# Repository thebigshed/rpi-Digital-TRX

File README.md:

# rpi-Digital-TRX

A stand-alone digital voice network radio on a Raspberry Pi 4 or Pi Zero 2 W. It is the hardware version of
[Digital Transceiver](https://github.com/thebigshed/digital-transceiver): it listens and
transmits on DMR, D-Star, YSF, P25, NXDN and M17, and receives DAPNET pages, over Wi-Fi.
There's no desktop. It boots straight into the radio, and you drive it from a front panel: mode
buttons with RGB LEDs, a channel knob, a volume knob and a PTT button, with a 20×4 LCD.

## Hardware

| Part | Used for | Connection |
|---|---|---|
| Raspberry Pi 4, or Pi Zero 2 W | Runs everything | — |
| NW Digital Radio DV3000 (ASSY1101, AMBE-3000R) | AMBE / AMBE+2 encode and decode in hardware: DMR, D-Star, YSF (DN), NXDN | First 26 header pins: serial port `/dev/ttyAMA0` at 230400 baud, reset on GPIO 4 |
| 20×4 LCD (HD44780) with a PCF8574 I2C backpack | Display | I2C at 0x27 or 0x3F, on the 5 V side of an I2C level shifter |
| Front panel ([wiring](docs/wiring.md)) | Six mode buttons, Menu, PTT, two KY-040 rotary encoders (channel and volume) | GPIO, through a 40-pin splitter |
| Two MCP23017 I/O expander modules | The seven common-cathode RGB LEDs (six modes and status) | I2C at 0x21 and 0x22, powered from 5 V on the 5 V side of the level shifter |
| USB headset | Speaker and microphone; its call button toggles PTT | USB |
| Adafruit RGB LCD Pi Plate (optional) | The old display and five buttons, used if the 20×4 isn't fitted | I2C at 0x20 |

The AMBE board sits on the first 26 header pins, and the panel is wired to the other side of a
"1 to 2" header splitter. They use different pins: the AMBE board uses the serial port
(GPIO 14/15) and GPIO 4, and the panel uses I2C (GPIO 2/3) and other GPIO pins. See
[docs/wiring.md](docs/wiring.md).

### Codecs

| Mode | Codec | Where it runs |
|---|---|---|
| DMR, NXDN, YSF DN | AMBE+2 | AMBE board |
| D-Star | AMBE | AMBE board |
| P25, YSF VW | IMBE | Software (OP25 / mbelib), easily fast enough on a Pi 4 |
| M17 | Codec2 | Software |

## Design

- **OS**: a minimal Linux image built with [Buildroot](https://buildroot.org) (2026.02 LTS).
  It has no desktop. It holds only what the radio needs: Qt 6 Core and Network (no Qt GUI,
  fonts or display platform), PulseAudio (system mode), wpa_supplicant, chrony, Dropbear SSH and
  i2c-tools.
- **App** (`app/`): the radio. It started as the Digital Transceiver desktop app and is now
  cut down to what the Pi needs: there are no windows or dialogs, and it is a plain Qt Core
  program. It is in three layers:
  - `Radio` (`Radio.cpp`, `RadioNet.cpp`): networks, decoding, calls, transmit, logs and
    recordings. It has no user interface.
  - `FrontPanel`: what the display shows and what each control does. It knows nothing about
    the hardware: displays implement `Display`, and input devices call `press()`,
    `release()`, `turn()` and `togglePtt()`.
  - Hardware: `GpioPanel` (the panel's buttons and encoders, as kernel GPIO events),
    `LedPanel` (the LEDs), `Lcd2004` (the 20×4 display), `LcdPlate` (the old 16×2 plate), `HeadsetButtons` (the
    headset's call button) and `SimPanel` (a stand-in for testing on a PC). Each part is
    optional; the radio logs what it can't find and carries on.

  Settings, call logs and recordings are the same as the desktop app's, so its
  `settings.json` can be copied over.
- **Display** (20×4):

  ```
  DSTR REF001 E  12:41     TX mode, where it transmits, time
  M6OZE            DSTR    the call on air: callsign and mode
  Ozzy                     name
  >CQCQCQ          0:07    target and call time
  ```

  When no call is on air, lines 2 and 3 show the last call heard, and the bottom line shows the
  IP address and volume, or a problem (a failed login, or the Pi-Star online). While browsing destinations it
  shows the one selected and the next. If the 20×4 isn't fitted, the Adafruit plate's 16×2
  shows a two-line version.
- **Controls** (full details in [docs/wiring.md](docs/wiring.md#what-the-controls-do)):

  | Control | Action |
  |---|---|
  | Mode button | Tap: listen to the mode or not. Hold: make it the TX mode |
  | Channel knob | Turn: step through the TX mode's destinations (reflectors, talkgroups, and for DMR the talkgroups listed in `settings.json`). Push: go there. Push and turn: D-Star / M17 module letter |
  | Volume knob | Turn: volume. Push: mute |
  | PTT | Hold to talk |
  | Menu | Tap: back. Hold 3 s: shut down; unplug when the display says "Safe to unplug" |
  | Headset call ("Teams") button | PTT on / off: press to start transmitting, press again to stop (the button only clicks, so it can't be held) |
  | LCD plate | Select: PTT, or go to the destination shown. Up / Down: TX mode. Left / Right: browse |

- **LEDs**: each mode's LED is green when listening, red when it's the TX mode (yellow for
  both) and blue while a call is on air in it. The status LED is red while transmitting, green
  while receiving and blue for a network problem or an unread page.

- **AMBE board**: the app opens the DV3000 with `--ambe /dev/ttyAMA0`. It resets the board on
  GPIO 4 (header pin 7) and talks to it at 230400 baud using DVSI's packet protocol
  (`app/src/AmbeChip.cpp`).
  - D-Star frames go to the chip as they are.
  - DMR, YSF DN and NXDN go to the chip as the 49 AMBE+2 voice bits, after mbelib's error
    correction (rate 34). The chip's bit order differs from mbelib's; the mapping was measured
    on the chip and is built in.
  - The chip has one decoder, so it follows one call at a time; any other call is decoded in
    software.
  - P25 (IMBE) and M17 (Codec2) are always decoded in software.
  - Check a chip with
    `digital-transceiver --ambe /dev/ttyAMA0 --ambe-test recording.wav`. It runs a recording
    through every chip and software combination and compares the result.

## Building

| Board | Command | Image |
|---|---|---|
| Raspberry Pi 4 | `./build.sh` | `output/images/sdcard.img` |
| Raspberry Pi Zero 2 W | `BOARD=zero2w ./build.sh` | `output-zero2w/images/sdcard.img` |

The first build for a board fetches Buildroot 2026.02.3 (once) and builds everything, which
takes a while. Each board has its own output folder, and the downloaded sources are shared. The
app is built from `app/` in this project. To rebuild only the app after changing it, run
`./build.sh digital-transceiver-rebuild all`, with `BOARD=zero2w` in front for the Zero.

`build.sh` reconfigures Buildroot when `external/configs/dtrx.fragment` or the board's fragment
changes. Buildroot leaves removed packages in the image until a clean build, so after removing
any, run `./build.sh clean all`.

### Raspberry Pi Zero 2 W

The Zero 2 W image runs the same software with the same hardware: the DV3000 fits the first 26
header pins, and the front panel wiring is unchanged. The differences are:

- **USB:** the headset goes in the **USB** port (the inner micro-USB, not PWR IN) through a
  micro-USB OTG adapter. Anything else needs a small hub.
- **No Ethernet:** Wi-Fi is the only network, so `wpa_supplicant.conf` must be on the boot
  partition before the first boot. Wi-Fi is 2.4 GHz only.
- **No analog audio:** the USB headset is the only audio device.
- **Header:** the plain Zero 2 W has no header fitted. Use a "WH" board, or solder one on.
- **Power:** a 5 V 2.5 A supply is plenty.

### Trying the app on a PC

The app also builds on a Linux PC with Qt 6 (Core and Network) and, for M17, Codec2:

```sh
cmake -S app -B app/build && cmake --build app/build -j
app/build/digital-transceiver --sim
```

With `--sim` (or `--sim-16x2` for the plate's layout), the display and LEDs are printed to the terminal and the controls are typed, one
per line (`+` = press, `-` = release): `1+`…`6-` the mode buttons, `t+`/`t-` and `v+`/`v-` turn
the channel and volume knobs, `k+`/`k-` push the channel knob, `m` pushes the volume knob,
`p+`/`p-` is PTT, `n+`/`n-` Menu and `h` the headset button. `s`, `u`, `d`, `l` and `r` are the
LCD plate's buttons. It uses the PC's settings in
`~/.config/digital-transceiver/digital-transceiver/`, so it logs in to the networks with
them; don't run it while the radio or the desktop app is online with the same IDs.

## Setting up the SD card

1. Write the board's image to the card (`output/images/sdcard.img` for the Pi 4,
   `output-zero2w/images/sdcard.img` for the Zero 2 W), for example with
   `sudo dd if=output/images/sdcard.img of=/dev/sdX bs=4M conv=fsync`. Write to the whole card
   (`/dev/sdX`), not a partition (`/dev/sdX1`).
2. On the card's boot partition (FAT, readable on any PC), add:

   | File | What it's for |
   |---|---|
   | `wpa_supplicant.conf` | Your Wi-Fi network; copy `boot-examples/wpa_supplicant.conf` and fill it in |
   | `settings.json` | Your Digital Transceiver settings; copy the desktop app's `~/.config/digital-transceiver/digital-transceiver/settings.json` |
   | `authorized_keys` | Optional: SSH public keys, for `ssh root@dtrx` |

   `settings.json` is copied in on the first boot and then renamed `settings.json.applied`, so
   changes made on the radio are kept.
3. Plug in the USB headset and boot. To turn the radio off, hold Menu for 3 seconds and unplug
   it when the display says "Safe to unplug". The app's log is `/var/log/dtrx.log`, and its event log
   is in `/root/.local/share/digital-transceiver/digital-transceiver/events.log`.

Don't run the radio and the desktop app (or a Pi-Star) at the same time with the same
settings: they would log in to the networks with the same IDs. Give the Pi its own DMR hotspot
ID (for example your DMR ID plus `03`) in its `settings.json`.

## Layout

```
build.sh            Configure and build the SD card image
app/                The radio app (CMake, Qt 6 Core and Network)
  src/              Radio, FrontPanel, the hardware drivers, decoders and network clients
  third_party/      mbelib (AMBE / IMBE decoding) and the OP25 vocoder (encoding)
external/           Buildroot external tree (BR2_EXTERNAL "DTRX")
  configs/          dtrx.fragment (all boards), rpi4.fragment and zero2w.fragment: added to
                    Buildroot's raspberrypi4_64 / raspberrypizero2w_64 defconfig
  package/          codec2, and digital-transceiver (built from app/)
  board/common/     post-build.sh and the rootfs overlay, for all boards
                    (init scripts: boot-partition config, Wi-Fi, the app)
  board/rpi4/       Pi 4 firmware config.txt and cmdline.txt
  board/zero2w/     Zero 2 W firmware config.txt and cmdline.txt
boot-examples/      Example files for the boot partition
buildroot/          Buildroot (fetched by build.sh, not committed)
output/             Pi 4 build output (not committed)
output-zero2w/      Zero 2 W build output (not committed)
```

## Next steps

1. **Menu**: a menu for RX modes, DMR talkgroup, volume and IP address (a long Menu press is
   now shutdown, so it will need another way in, such as pushing both knobs).

## Licence

GPL-3.0-or-later, the same as Digital Transceiver, whose code it reuses. mbelib (`app/third_party/mbelib`)
and OP25 (`app/third_party/op25_vocoder`) keep their own licences.

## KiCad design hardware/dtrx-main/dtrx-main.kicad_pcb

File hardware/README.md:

# Digital TRX hardware (KiCad 9)

Two boards joined by a 20-way IDC ribbon cable (pin 1 to pin 1):

| Project | What's on it |
|---|---|
| `dtrx-main/` | Raspberry Pi Zero 2 W (face down on a 2x20 socket, ports at the left edge), the DV3000 AMBE-3000 board on a 2x13 header, 5 V input with a PTC fuse, and the ribbon header |
| `dtrx-panel/` | The front panel: 20x4 LCD in the middle, three mode buttons with RGB LEDs down each side, volume encoder and Menu bottom left, PTT and channel encoder bottom right, the status LED under the display. J2 for the LCD's I2C backpack. On the back: both MCP23017 LED drivers, the I2C level shifter and the pull-ups |

Open `dtrx-main/dtrx-main.kicad_pro` or `dtrx-panel/dtrx-panel.kicad_pro` in KiCad. Each has a
schematic, a routed 2-layer PCB with a ground pour on both sides, and a PDF of the schematic.

Both boards were autorouted with Freerouting by `route.py`, ground included, so no pin depends
on the pour. DRC is clean on both boards: every connection made, the PCB matching its schematic,
no warnings. Where tracks box a ground pin in so the pour's thermal spokes can't reach it,
`route.py` connects that one pin solidly to the pour instead (a handful of header pins).

The design matches the app as it is. Buttons and encoders go to the same Pi GPIO pins, the LED
drivers sit at 0x21 and 0x22, and the LCD keeps its own I2C backpack (0x27 or 0x3F). So no
software changes are needed apart from building the image for the Pi Zero 2 W.

## Regenerating

`gen_boards.py` writes both projects from scratch: `python3 hardware/gen_boards.py` (it needs KiCad's
`pcbnew` Python module). Re-running it **overwrites** any routing or hand changes, so make design
changes in the script first, then route again with `python3 hardware/route.py` (needs Java and the
[Freerouting](https://github.com/freerouting/freerouting/releases) jar; see the top of the script). Part values, pin assignments, positions and the LCD
dimensions are all near the top of the script.

## Ribbon (J3 on the main board, J1 on the panel)

| Pin | Signal | Pin | Signal |
|---|---|---|---|
| 1 | +5 V | 2 | GND |
| 3 | +3.3 V | 4 | SDA (3.3 V) |
| 5 | SCL (3.3 V) | 6 | GND |
| 7 | PTT (GPIO 23) | 8 | Menu (GPIO 26) |
| 9 | Channel A (GPIO 24) | 10 | Channel B (GPIO 27) |
| 11 | Channel push / Link (GPIO 22) | 12 | Volume A (GPIO 20) |
| 13 | Volume B (GPIO 21) | 14 | Volume push / Mute (GPIO 18) |
| 15 | DMR (GPIO 5) | 16 | D-Star (GPIO 6) |
| 17 | YSF (GPIO 12) | 18 | P25 (GPIO 13) |
| 19 | NXDN (GPIO 19) | 20 | M17 (GPIO 16) |

The I2C bus crosses the ribbon at 3.3 V, and a two-FET level shifter on the panel lifts it to 5 V
for the MCP23017s and the LCD backpack. So the LEDs and the LCD run from 5 V, as on the hand-wired
panel. The MCP23017 address pins are fixed by copper (no jumpers to bridge): U1 is 0x21, U2 is 0x22.

## Check before ordering boards

- **LCD:** the 2004A keeps its I2C backpack and is only bolted to the panel, so the footprint
  `lib/dtrx.pretty/LCD_2004A_98x60` is just the outline and four M3 holes (93 x 55 mm apart on the
  common 98 x 60 mm module). Measure yours; the numbers are `LCD_W`, `LCD_H` and `LCD_HOLES` in
  the script. Use standoffs tall enough for the backpack to clear the panel (about 15 mm), and a
  short 4-way female-female lead from the backpack's GND, VCC, SDA and SCL to J2 (marked LCD, just
  left of the display, same pin order). Set the contrast with the backpack's own trimmer.
- **DV3000:** J2 on the main board copies the Pi's pins 1-26, with pin 1 and the odd row in the
  same places as on a Pi. The board's outline and mounting holes aren't in the design, because I
  don't have its dimensions. Check it fits between the Pi and the ribbon header, and add standoff
  holes.
- **RGB LEDs:** footprint and symbol are common cathode, legs in the order red, cathode
  (longest), green, blue. Check against your LEDs.
- **Encoders:** footprint is the Alps EC11E with push switch, the same part as on the KY-040
  modules. The panel has its own 10k pull-ups, so bare encoders work.
- **Buttons:** 12 mm tactile switches (4 pins). Change the footprint in the script for other
  switches.
- **Pi Zero 2 W:** solder a normal male 2x20 header to the Pi and mount it face down onto a female
  2x20 socket on the main board. Its micro-USB OTG port takes the USB headset, through an OTG
  adapter. Power comes in at J1 (5 V, 2.5 A supply recommended), not the Pi's power USB socket.

## Software for the Pi Zero 2 W

Build the Zero 2 W image with `BOARD=zero2w ./build.sh` (see the main README). The app needs no
changes: it finds the GPIO chip by its `pinctrl-bcm2835` label, which the Zero 2 W uses.

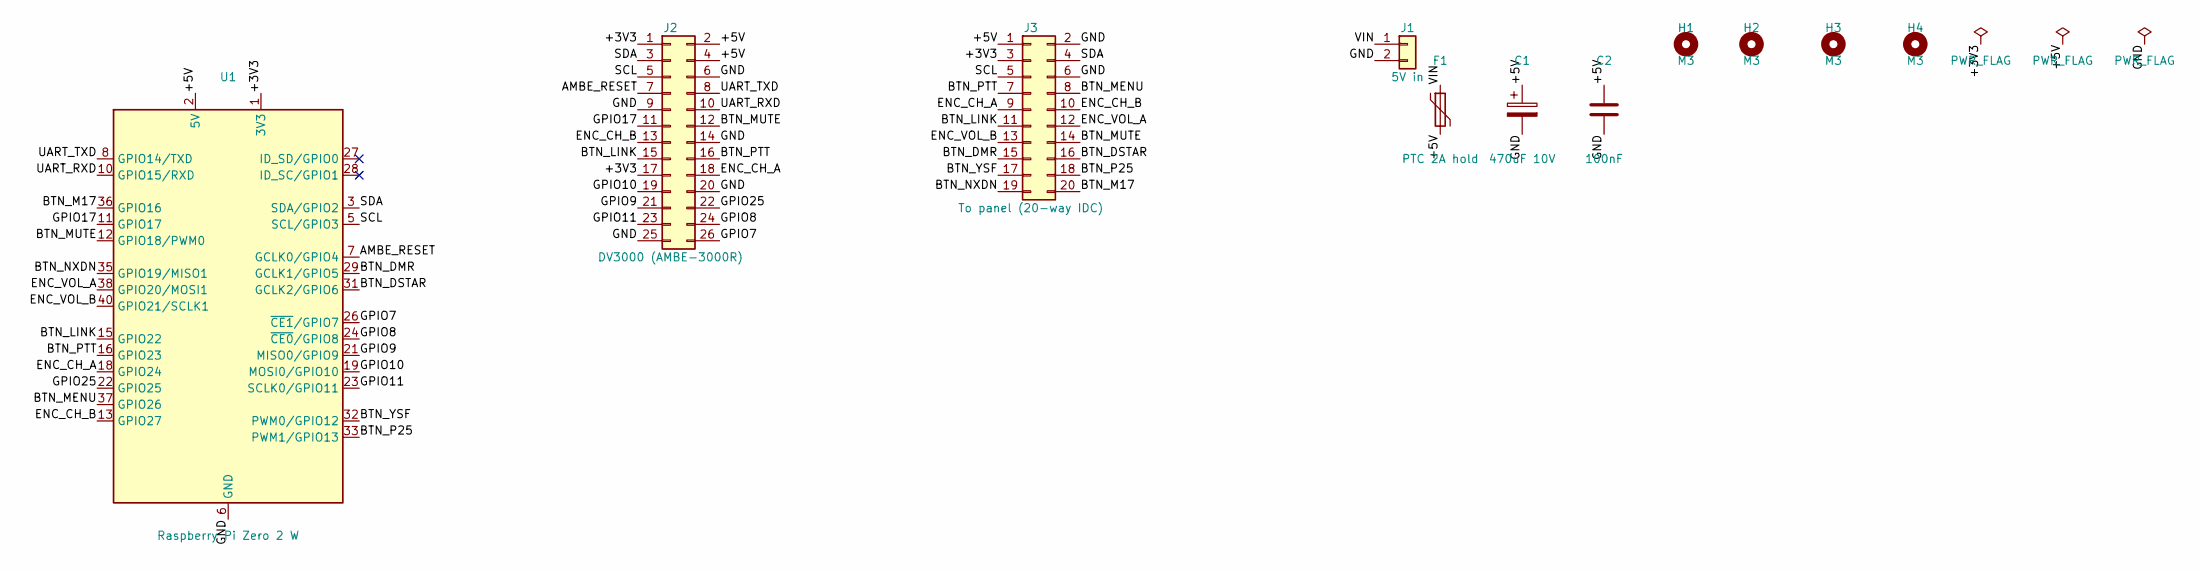
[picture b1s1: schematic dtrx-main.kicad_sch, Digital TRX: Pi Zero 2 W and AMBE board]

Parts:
C1: 470uF 10V; CP_Radial_D8.0mm_P3.50mm
C2: 100nF; C_Disc_D5.0mm_W2.5mm_P5.00mm
F1: PTC 2A hold; Fuse_Bourns_MF-RG300
H1, H2, H3, H4: M3; MountingHole_3.2mm_M3
J1: 5V in; TerminalBlock_Phoenix_MKDS-1,5-2_1x02_P5.00mm_Horizontal
J2: DV3000 (AMBE-3000R); PinHeader_2x13_P2.54mm_Vertical
J3: To panel (20-way IDC); IDC-Header_2x10_P2.54mm_Vertical
U1: Raspberry Pi Zero 2 W; Raspberry_Pi_Zero_Socketed_THT_FaceDown_MountingHoles

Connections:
/+3V3: J2.1, J2.17, J3.3, U1.1 (3V3), U1.17 (3V3)
/+5V: C1.1, C2.1, F1.2, J2.2, J2.4, J3.1, U1.2 (5V), U1.4 (5V)
/AMBE_RESET: J2.7, U1.7 (GCLK0/GPIO4)
/BTN_DMR: J3.15, U1.29 (GCLK1/GPIO5)
/BTN_DSTAR: J3.16, U1.31 (GCLK2/GPIO6)
/BTN_LINK: J2.15, J3.11, U1.15 (GPIO22)
/BTN_M17: J3.20, U1.36 (GPIO16)
/BTN_MENU: J3.8, U1.37 (GPIO26)
/BTN_MUTE: J2.12, J3.14, U1.12 (GPIO18/PWM0)
/BTN_NXDN: J3.19, U1.35 (GPIO19/MISO1)
/BTN_P25: J3.18, U1.33 (PWM1/GPIO13)
/BTN_PTT: J2.16, J3.7, U1.16 (GPIO23)
/BTN_YSF: J3.17, U1.32 (PWM0/GPIO12)
/ENC_CH_A: J2.18, J3.9, U1.18 (GPIO24)
/ENC_CH_B: J2.13, J3.10, U1.13 (GPIO27)
/ENC_VOL_A: J3.12, U1.38 (GPIO20/MOSI1)
/ENC_VOL_B: J3.13, U1.40 (GPIO21/SCLK1)
/GND: C1.2, C2.2, J1.2, J2.6, J2.9, J2.14, J2.20, J2.25, J3.2, J3.6, U1.6 (GND), U1.9 (GND), U1.14 (GND), U1.20 (GND), U1.25 (GND), U1.30 (GND), U1.34 (GND), U1.39 (GND)
/GPIO7: J2.26, U1.26 (~CE1/GPIO7)
/GPIO8: J2.24, U1.24 (~CE0/GPIO8)
/GPIO9: J2.21, U1.21 (MISO0/GPIO9)
/GPIO10: J2.19, U1.19 (MOSI0/GPIO10)
/GPIO11: J2.23, U1.23 (SCLK0/GPIO11)
/GPIO17: J2.11, U1.11 (GPIO17)
/GPIO25: J2.22, U1.22 (GPIO25)
/SCL: J2.5, J3.5, U1.5 (SCL/GPIO3)
/SDA: J2.3, J3.4, U1.3 (SDA/GPIO2)
/UART_RXD: J2.10, U1.10 (GPIO15/RXD)
/UART_TXD: J2.8, U1.8 (GPIO14/TXD)
/VIN: F1.1, J1.1

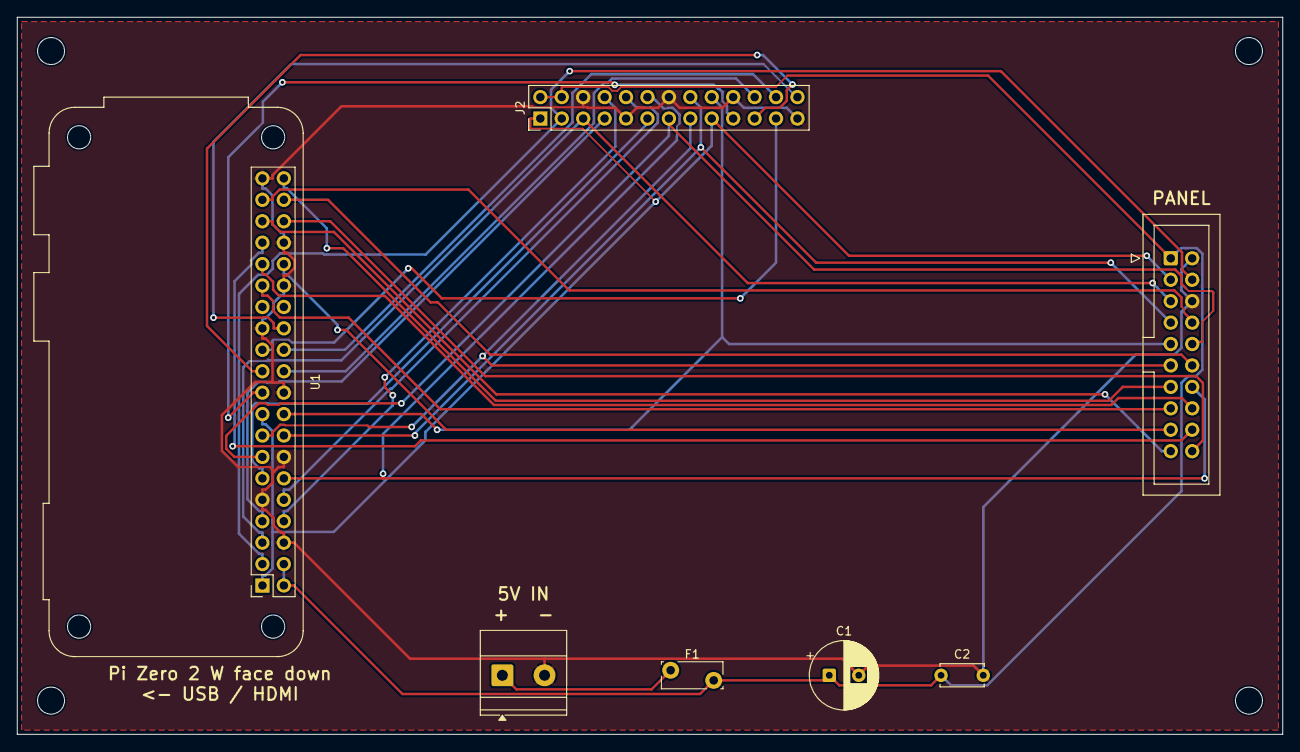
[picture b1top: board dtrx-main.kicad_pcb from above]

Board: 2 copper layers, 150.0 x 85.0 mm, 11 parts (0 on the bottom side), 30 nets.

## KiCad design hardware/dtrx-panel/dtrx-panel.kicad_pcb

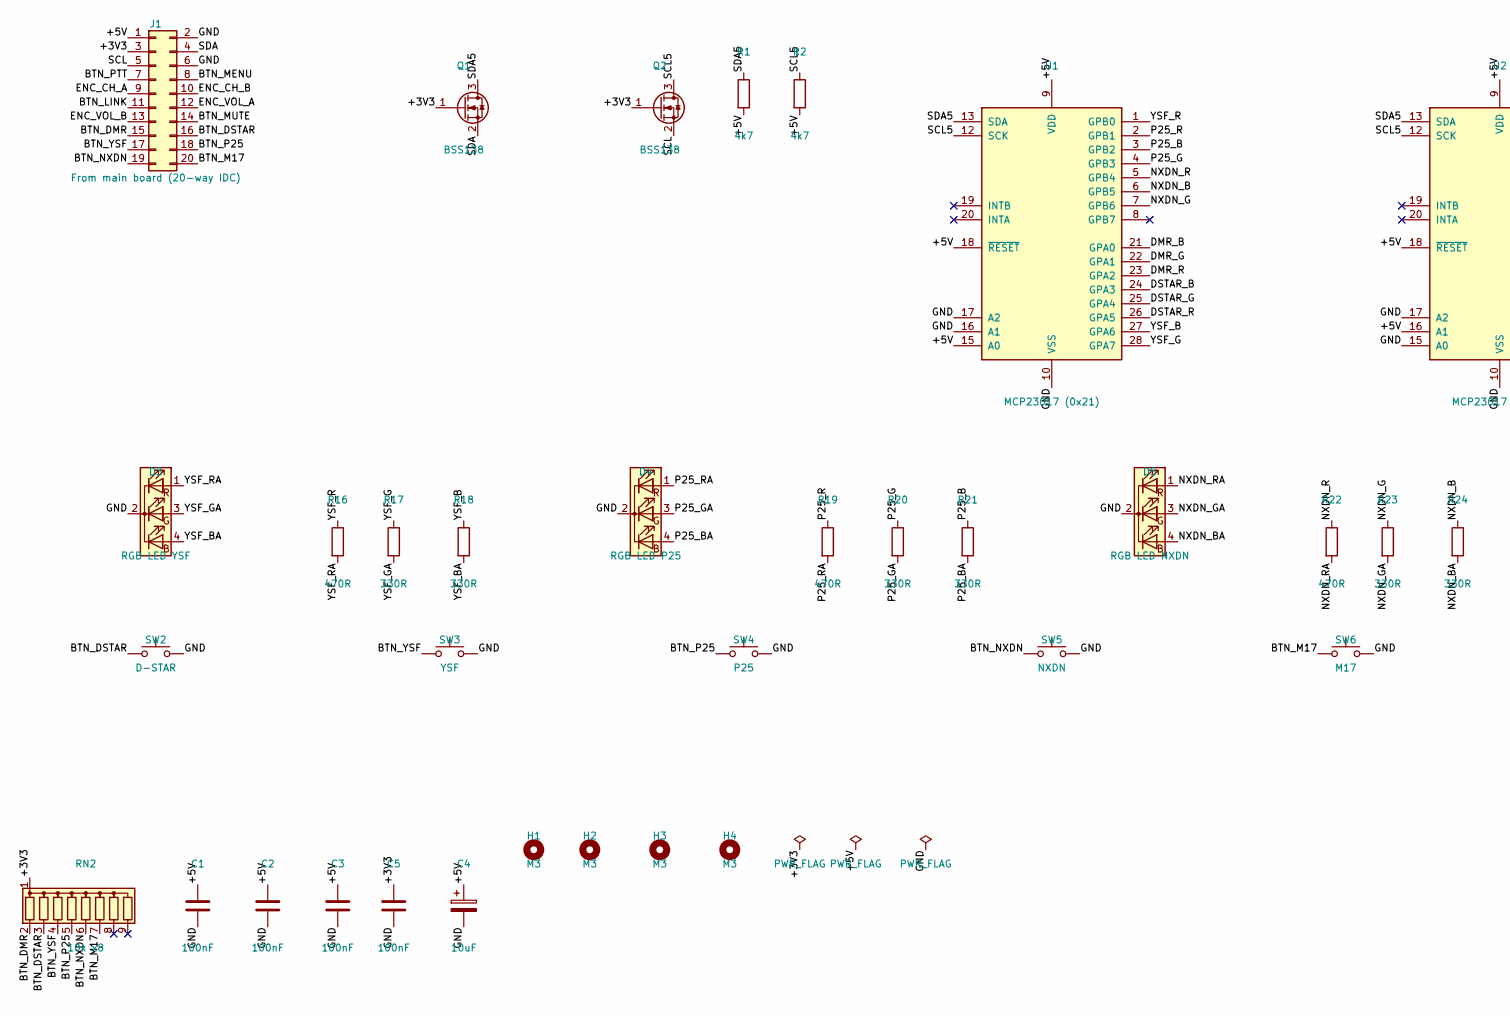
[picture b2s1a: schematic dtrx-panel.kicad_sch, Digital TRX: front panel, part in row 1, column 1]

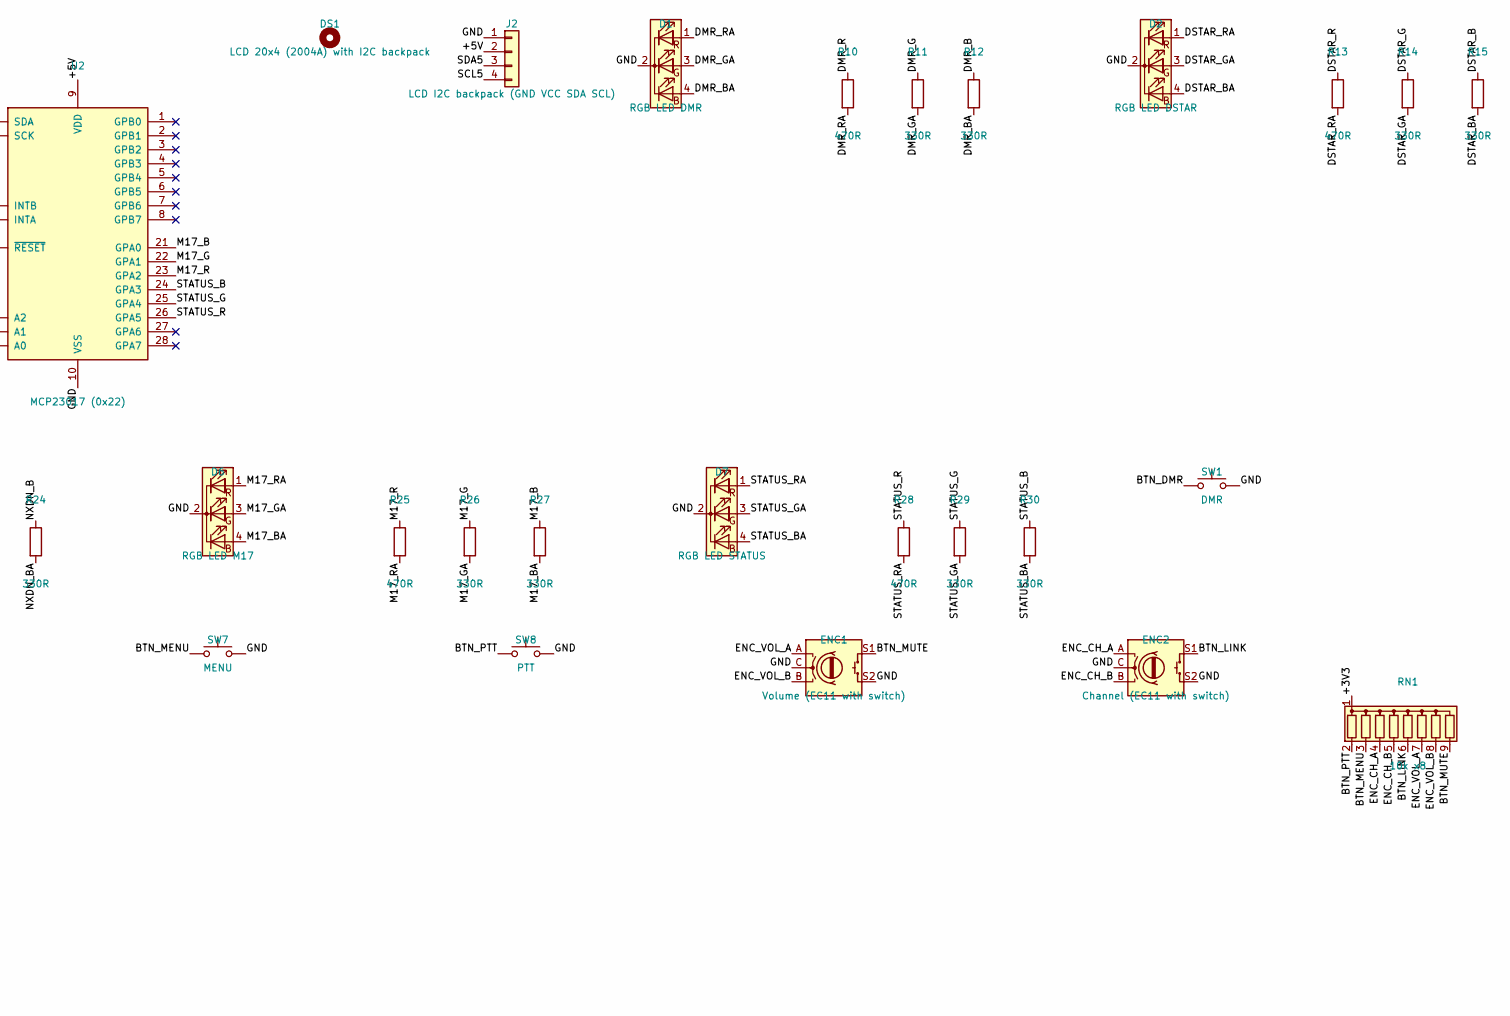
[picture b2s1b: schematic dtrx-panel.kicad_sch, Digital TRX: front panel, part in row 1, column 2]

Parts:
C1, C2, C3, C5: 100nF; C_Disc_D5.0mm_W2.5mm_P5.00mm
C4: 10uF; CP_Radial_D5.0mm_P2.00mm
D1: RGB LED DMR; LED_D5.0mm-4_RGB
D2: RGB LED DSTAR; LED_D5.0mm-4_RGB
D3: RGB LED YSF; LED_D5.0mm-4_RGB
D4: RGB LED P25; LED_D5.0mm-4_RGB
D5: RGB LED NXDN; LED_D5.0mm-4_RGB
D6: RGB LED M17; LED_D5.0mm-4_RGB
D7: RGB LED STATUS; LED_D5.0mm-4_RGB
DS1: LCD 20x4 (2004A) with I2C backpack; LCD_2004A_98x60
ENC1: Volume (EC11 with switch); RotaryEncoder_Alps_EC11E-Switch_Vertical_H20mm
ENC2: Channel (EC11 with switch); RotaryEncoder_Alps_EC11E-Switch_Vertical_H20mm
H1, H2, H3, H4: M3; MountingHole_3.2mm_M3
J1: From main board (20-way IDC); IDC-Header_2x10_P2.54mm_Vertical
J2: LCD I2C backpack (GND VCC SDA SCL); PinHeader_1x04_P2.54mm_Vertical
Q1, Q2: BSS138; SOT-23
R1, R2: 4k7; R_Axial_DIN0207_L6.3mm_D2.5mm_P2.54mm_Vertical
R10, R13, R16, R19, R22, R25, R28: 470R; R_Axial_DIN0207_L6.3mm_D2.5mm_P2.54mm_Vertical
R11, R12, R14, R15, R17, R18, R20, R21, R23, R24, R26, R27, R29, R30: 330R; R_Axial_DIN0207_L6.3mm_D2.5mm_P2.54mm_Vertical
RN1, RN2: 10k x8; R_Array_SIP9
SW1: DMR; SW_PUSH-12mm
SW2: D-STAR; SW_PUSH-12mm
SW3: YSF; SW_PUSH-12mm
SW4: P25; SW_PUSH-12mm
SW5: NXDN; SW_PUSH-12mm
SW6: M17; SW_PUSH-12mm
SW7: MENU; SW_PUSH-12mm
SW8: PTT; SW_PUSH-12mm
U1: MCP23017 (0x21); DIP-28_W7.62mm
U2: MCP23017 (0x22); DIP-28_W7.62mm

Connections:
/+3V3: C5.1, J1.3, Q1.1 (G), Q2.1 (G), RN1.1 (common), RN2.1 (common)
/+5V: C1.1, C2.1, C3.1, C4.1, J1.1, J2.2, R1.2, R2.2, U1.9 (VDD), U1.15 (A0), U1.18 (~RESET), U2.9 (VDD), U2.16 (A1), U2.18 (~RESET)
/BTN_DMR: J1.15, RN2.2 (R1), SW1.1
/BTN_DSTAR: J1.16, RN2.3 (R2), SW2.1
/BTN_LINK: ENC2.S1, J1.11, RN1.6 (R5)
/BTN_M17: J1.20, RN2.7 (R6), SW6.1
/BTN_MENU: J1.8, RN1.3 (R2), SW7.1
/BTN_MUTE: ENC1.S1, J1.14, RN1.9 (R8)
/BTN_NXDN: J1.19, RN2.6 (R5), SW5.1
/BTN_P25: J1.18, RN2.5 (R4), SW4.1
/BTN_PTT: J1.7, RN1.2 (R1), SW8.1
/BTN_YSF: J1.17, RN2.4 (R3), SW3.1
/DMR_B: R12.1, U1.21 (GPA0)
/DMR_BA: D1.4 (BA), R12.2
/DMR_G: R11.1, U1.22 (GPA1)
/DMR_GA: D1.3 (GA), R11.2
/DMR_R: R10.1, U1.23 (GPA2)
/DMR_RA: D1.1 (RA), R10.2
/DSTAR_B: R15.1, U1.24 (GPA3)
/DSTAR_BA: D2.4 (BA), R15.2
/DSTAR_G: R14.1, U1.25 (GPA4)
/DSTAR_GA: D2.3 (GA), R14.2
/DSTAR_R: R13.1, U1.26 (GPA5)
/DSTAR_RA: D2.1 (RA), R13.2
/ENC_CH_A: ENC2.A, J1.9, RN1.4 (R3)
/ENC_CH_B: ENC2.B, J1.10, RN1.5 (R4)
/ENC_VOL_A: ENC1.A, J1.12, RN1.7 (R6)
/ENC_VOL_B: ENC1.B, J1.13, RN1.8 (R7)
/GND: C1.2, C2.2, C3.2, C4.2, C5.2, D1.2 (K), D2.2 (K), D3.2 (K), D4.2 (K), D5.2 (K), D6.2 (K), D7.2 (K), ENC1.C, ENC1.S2, ENC2.C, ENC2.S2, J1.2, J1.6, J2.1, SW1.2, SW2.2, SW3.2, SW4.2, SW5.2, SW6.2, SW7.2, SW8.2, U1.10 (VSS), U1.16 (A1), U1.17 (A2), U2.10 (VSS), U2.15 (A0), U2.17 (A2)
/M17_B: R27.1, U2.21 (GPA0)
/M17_BA: D6.4 (BA), R27.2
/M17_G: R26.1, U2.22 (GPA1)
/M17_GA: D6.3 (GA), R26.2
/M17_R: R25.1, U2.23 (GPA2)
/M17_RA: D6.1 (RA), R25.2
/NXDN_B: R24.1, U1.6 (GPB5)
/NXDN_BA: D5.4 (BA), R24.2
/NXDN_G: R23.1, U1.7 (GPB6)
/NXDN_GA: D5.3 (GA), R23.2
/NXDN_R: R22.1, U1.5 (GPB4)
/NXDN_RA: D5.1 (RA), R22.2
/P25_B: R21.1, U1.3 (GPB2)
/P25_BA: D4.4 (BA), R21.2
/P25_G: R20.1, U1.4 (GPB3)
/P25_GA: D4.3 (GA), R20.2
/P25_R: R19.1, U1.2 (GPB1)
/P25_RA: D4.1 (RA), R19.2
/SCL: J1.5, Q2.2 (S)
/SCL5: J2.4, Q2.3 (D), R2.1, U1.12 (SCK), U2.12 (SCK)
/SDA: J1.4, Q1.2 (S)
/SDA5: J2.3, Q1.3 (D), R1.1, U1.13 (SDA), U2.13 (SDA)
/STATUS_B: R30.1, U2.24 (GPA3)
/STATUS_BA: D7.4 (BA), R30.2
/STATUS_G: R29.1, U2.25 (GPA4)
/STATUS_GA: D7.3 (GA), R29.2
/STATUS_R: R28.1, U2.26 (GPA5)
/STATUS_RA: D7.1 (RA), R28.2
/YSF_B: R18.1, U1.27 (GPA6)
/YSF_BA: D3.4 (BA), R18.2
/YSF_G: R17.1, U1.28 (GPA7)
/YSF_GA: D3.3 (GA), R17.2
/YSF_R: R16.1, U1.1 (GPB0)
/YSF_RA: D3.1 (RA), R16.2

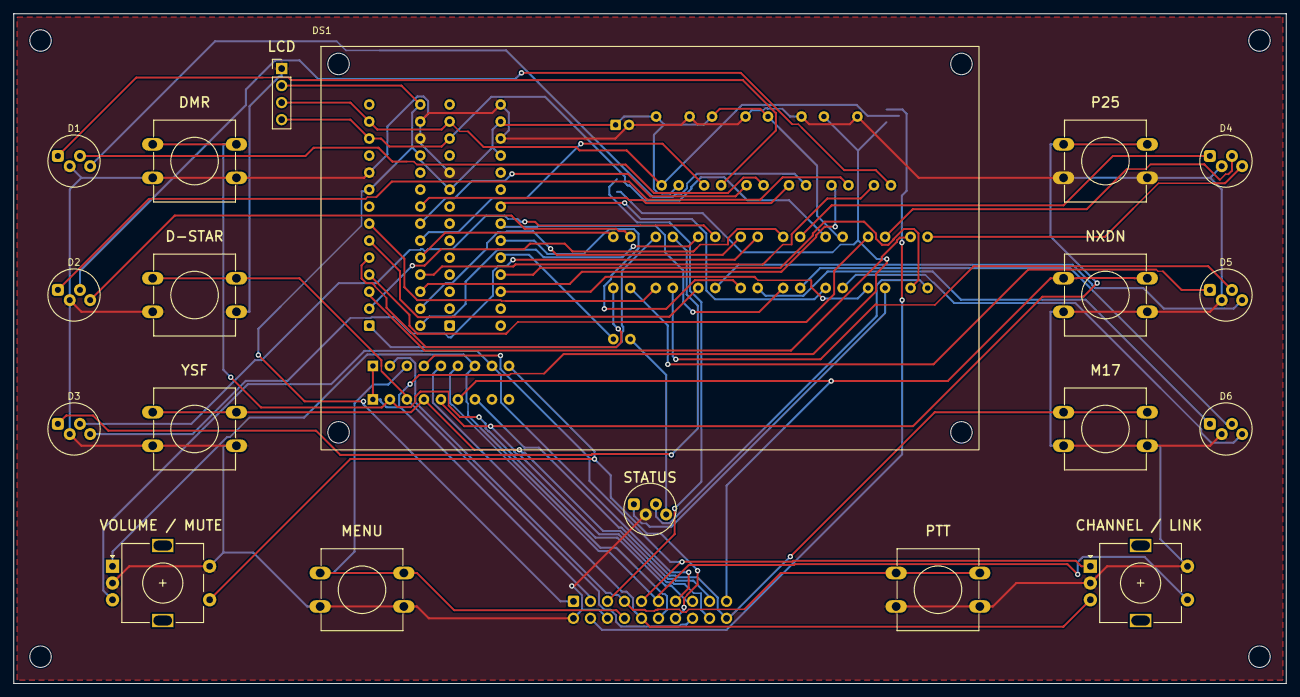
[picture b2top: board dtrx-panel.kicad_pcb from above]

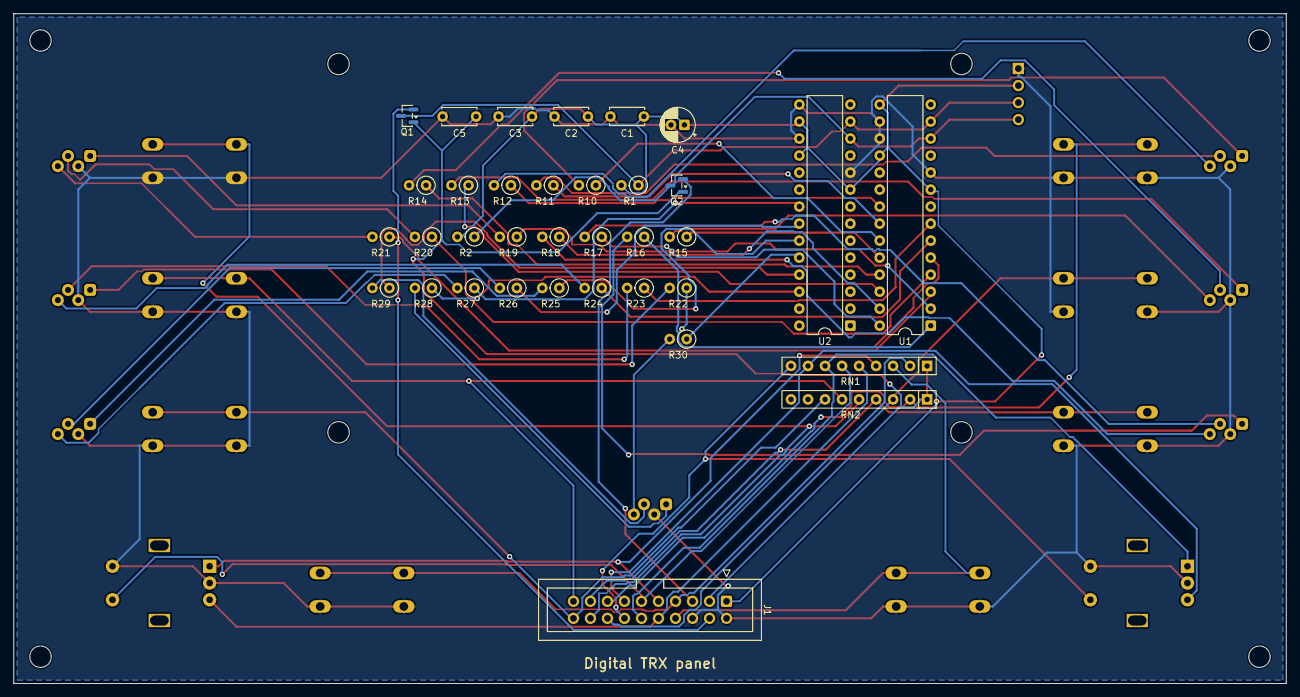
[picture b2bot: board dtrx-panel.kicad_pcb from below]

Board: 2 copper layers, 190.0 x 100.0 mm, 58 parts (35 on the bottom side), 63 nets.

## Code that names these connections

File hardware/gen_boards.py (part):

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    b = Board('dtrx-main', 'Digital TRX: Pi Zero 2 W and AMBE board', (150, 85))
    # Channel A is on GPIO 24 (pin 18): the DV3000 holds GPIO 17 (pin 11) low.
    pi = {1: '+3V3', 17: '+3V3', 2: '+5V', 4: '+5V', 3: 'SDA', 5: 'SCL', 7: 'AMBE_RESET',
          8: 'UART_TXD', 10: 'UART_RXD', 11: 'GPIO17', 12: 'BTN_MUTE', 13: 'ENC_CH_B',
          15: 'BTN_LINK', 16: 'BTN_PTT', 18: 'ENC_CH_A', 19: 'GPIO10', 21: 'GPIO9', 22: 'GPIO25',
          23: 'GPIO11', 24: 'GPIO8', 26: 'GPIO7', 29: 'BTN_DMR', 31: 'BTN_DSTAR', 32: 'BTN_YSF',
          33: 'BTN_P25', 35: 'BTN_NXDN', 36: 'BTN_M17', 37: 'BTN_MENU', 38: 'ENC_VOL_A',
          40: 'ENC_VOL_B'}
    for g in (6, 9, 14, 20, 25, 30, 34, 39):
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
    # LED drivers: module A at 0x21, module B at 0x22 (app/src/LedPanel.cpp)
    # each LED's pins run blue, green, red (as wired on the prototype panel)
    a_pins = {'GPA0': 'DMR_B', 'GPA1': 'DMR_G', 'GPA2': 'DMR_R', 'GPA3': 'DSTAR_B',
              'GPA4': 'DSTAR_G', 'GPA5': 'DSTAR_R', 'GPA6': 'YSF_B', 'GPA7': 'YSF_G',
              'GPB0': 'YSF_R', 'GPB1': 'P25_R', 'GPB2': 'P25_B', 'GPB3': 'P25_G',
              'GPB4': 'NXDN_R', 'GPB5': 'NXDN_B', 'GPB6': 'NXDN_G'}
    b_pins = {'GPA0': 'M17_B', 'GPA1': 'M17_G', 'GPA2': 'M17_R', 'GPA3': 'STATUS_B',
              'GPA4': 'STATUS_G', 'GPA5': 'STATUS_R'}
    mcp = flat_symbol('Interface_Expansion', 'MCP23017_SP')
    num = {name: n for n, name, *_ in sym_pins(mcp)}
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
